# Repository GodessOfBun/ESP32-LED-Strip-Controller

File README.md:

## Introduction:

This ESP32-C2 Based board is designed to control up to 5 channels of an LED Strip. Each channel is in theory capable of 4A up to 24V with the total current drawn from the board not exceeding 5A. Although in theory there isn't much preventing it from reaching 8A current(eFuse max) other than trace width and the bulk capacitor and so on.
Mosfet remains below 50c with a 99% duty cycle at 2.4A/24v @ 25KHz in testing. In theory, according to my calculations, it can easily handle 4A or even 4.5A/5A. above 4A is not recommended. It is compatible with Matter (using the code I'm too eepy and busy to upload right now) and HA with ESPHome. If you use HA  you might as well save yourself the trouble and use ESPHome as Matter can have it's own shortcomings.

Measured Channel FET rise time: 12.5ns.

eFuse can be skipped by shorting the VIN to EFUSE to the output with a wire.

The board is designed for 25KHz in mind but can be used with a lower or higher frequency within reason.

You can leave unused channnels empty and not solder them to save on cost. 

The EFUSE is connfigured to be triggered at 5.51A. It features a 150ms-300ms~ soft-start to prevent sparks when connecting the power.

Note: It features a 0201 test LED originally used as a fun challenge for soldering. I suggest changing it to a 0602/0402 package if using it in practice or debugging with it as it can be very challenging to solder.

A IPEX connector is used to debug and monitor the 3.3v rail ripple and transient performance. Note however that the 50 ohm termination seems to not be working, I will confirm why when the project is finished as it's not essential and works perfectly fine with a probe tip to BNC adapter as the probe is designed to be purposely lossy and cancel ringing. A BNC to IPEX Cable is recommended. Note that IPEX connectors are not meant for frequent unplugging and replugging. The socket is rated for 30-50 mating cycles

### Notes:
Frequency of 2.2MHz was chosen for the 3.3v rail to improve transient response and performance/size of the buck converter. Efficiency is not a big concern for such an application.
An eFuse (Hot-swap controller) was chosen for this board to prevent sparking upon plugging in and to reduce the required footprint for an ressetable poly fuse that can withstand 40-30v at 5A.

## Potential  Improvemtns:
- [ ] Add a factory reset button seperate from BOOT
- [ ] External antenna instead of built-in PCB
- [ ] Switch from ESP32-C2 to C3 or similiar for better matter compatbility and performance.
- [ ] Use a dedicated ESP32 IC instead of a pre-made module as the PCB is already 4 layers hence the impedance matching is very easy and does not add additional cost.
- [ ] Add a polymer/tantalum bulk cap for esp32 to reduce wifi transmission transients. This will require some consideration to prevent ringing at the output.
- [ ] Calculate and confirm feed-forward capacitor for the 3.3v rail. (It is picked based on gut feeling)
- [ ] Improve hand-solderability, use bigger TVS diodes.
- [ ] Add jumper for 3.3v from programming header.
- [ ] (?) Debug LED for each channel
- [ ] (?) RGB Indicator LED for when WiFI is connected and device is commisioned.
- [ ] (?) Software based SSFM solution for each channel to reduce EMI emitted from the LED Strips as they are difficult to shield and user assembled. For a simpler but less effective solution, Each channel can operate at a slightly different ferquency.
- [ ] (?) eFuse skip jumper.

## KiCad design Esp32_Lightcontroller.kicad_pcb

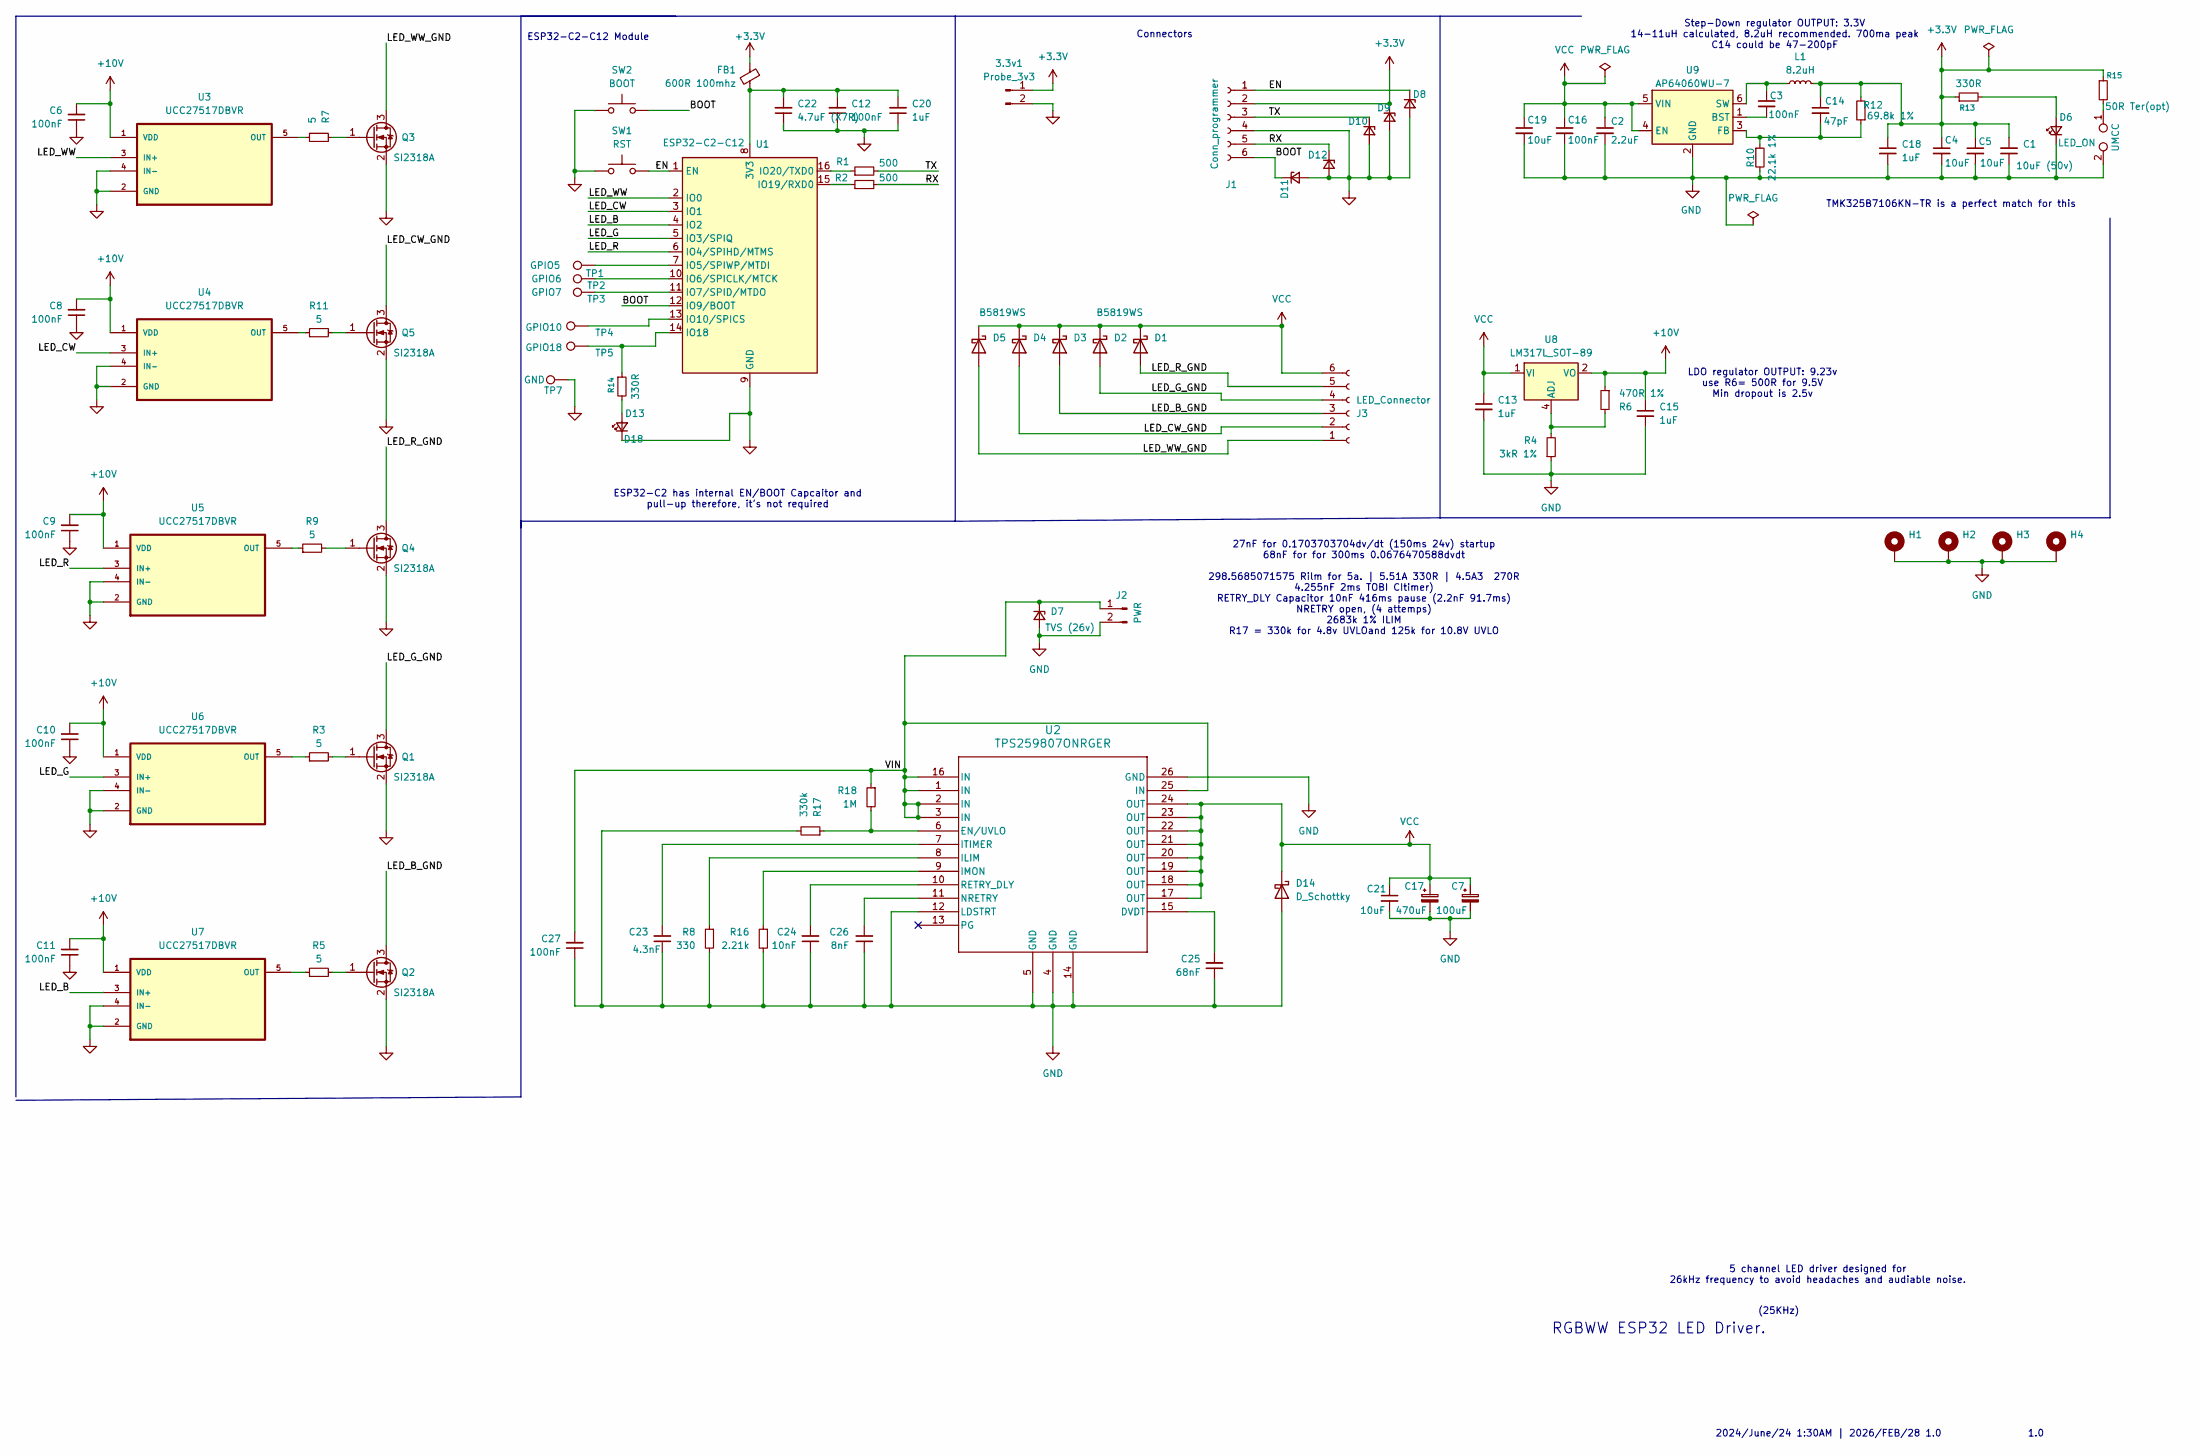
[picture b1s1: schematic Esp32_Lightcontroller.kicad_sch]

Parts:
3.3v1: Probe_3v3; Scope_probe_pad
C1: 10uF (50v); C_1210_3225Metric
C2: 2.2uF; C_1206_3216Metric
C3, C12, C16: 100nF; C_0603_1608Metric
C4, C5, C19, C21: 10uF; C_1210_3225Metric
C6, C8, C9, C10, C11, C27: 100nF; C_0402_1005Metric
C7: 100uF; CP_Elec_6.3x7.7
C13, C18, C20: 1uF; C_0805_2012Metric
C14: 47pF; C_0402_1005Metric
C15: 1uF; C_1206_3216Metric
C17: 470uF; CP_Radial_D10.0mm_P5.00mm
C22: 4.7uF (X7R); C_0805_2012Metric
C23: 4.3nF; C_0402_1005Metric
C24: 10nF; C_0402_1005Metric
C25: 68nF; C_0402_1005Metric
C26: 8nF; C_0402_1005Metric
D1, D5: B5819WS; D_SOD-323
D2, D3, D4: 1N5819WS; D_SOD-323
D6: LED_ON; LED_0603_1608Metric
D7: TVS (26v); D_SOD-123F
D8, D9, D10, D11, D12: 5v; D_SOD-523
D13: D18; LED_0201_0603Metric
D14: D_Schottky; D_SOD-123
FB1: 600R 100mhz; Ferrite_0603_1608Metric
H1, H2, H3, H4: MountingHole_Pad; MountingHole_3.2mm_M3_DIN965_Pad_TopBottom
J1: Conn_programmer; PinHeader_2x03_P1.27mm_Vertical
J2: PWR; TerminalBlock_CUI_TB007-508-02_1x02_P5.08mm_Horizontal
J3: LED_Connector; TerminalBlock_MaiXu_MX126-5.0-06P_1x06_P5.00mm
L1: 8.2uH; L_Coilcraft_XAL6060-XXX
Q1, Q2, Q3, Q4, Q5: SI2318A; SOT-23
R1, R2: 500; R_0603_1608Metric
R3, R5, R7, R9, R11: 5; R_0603_1608Metric
R4: 3kR 1%; R_0603_1608Metric
R6: 470R 1%; R_0603_1608Metric
R8: 330; R_0603_1608Metric
R10: 22.1k 1%; R_0603_1608Metric
R12: 69.8k 1%; R_0603_1608Metric
R13: 330R; R_0603_1608Metric
R14: 330R; R_0201_0603Metric
R15: 50R Ter(opt); R_0603_1608Metric
R16: 2.21k; R_0603_1608Metric
R17: 330k; R_0603_1608Metric
R18: 1M; R_0603_1608Metric
SW1: RST; SW_Push_SPST_NO_Alps_SKRK
SW2: BOOT; SW_Push_SPST_NO_Alps_SKRK
TP1: GPIO5; TestPoint_Pad_D1.5mm
TP2: GPIO6; TestPoint_Pad_D1.5mm
TP3: GPIO7; TestPoint_Pad_D1.5mm
TP4: GPIO10; TestPoint_Pad_D1.5mm
TP5: GPIO18; TestPoint_Pad_D1.5mm
TP6: UMCC; U.FL_Molex_MCRF_73412-0110_Vertical
TP7: GND; TestPoint_Pad_D1.5mm
U1: ESP32-C2-C12
U2: TPS259807ONRGER; VQFN24_RGE_TEX
U3, U4, U5, U6, U7: UCC27517DBVR; SOT95P280X145-5N; DigiKey_Part_Number 296-39527-1-ND
U8: LM317L_SOT-89; SOIC-8_3.9x4.9mm_P1.27mm
U9: AP64060WU-7; TSOT-23-6

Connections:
+3.3V: 3.3v1.1, C1.2, C4.1, C5.1, C14.1, C18.1, D9.1 (K), FB1.1, J1.2, L1.2, R12.2, R13.1, R15.1
+10V: C6.2, C8.2, C9.2, C10.2, C11.2, C15.1, R6.1, U3.1 (VDD), U4.1 (VDD), U5.1 (VDD), U6.1 (VDD), U7.1 (VDD), U8.2 (VO), U8.3 (VO), U8.6 (VO), U8.7 (VO)
/BOOT: D11.1 (K), J1.6, SW2.2, U1.12 (IO9/BOOT)
/EN: D8.1 (K), J1.1, SW1.2, U1.1 (EN)
/LED_B: U1.4 (IO2), U7.3 (IN+)
/LED_B_GND: D3.2 (A), J3.3, Q2.3 (D)
/LED_CW: U1.3 (IO1), U4.3 (IN+)
/LED_CW_GND: D4.2 (A), J3.2, Q5.3 (D)
/LED_G: U1.5 (IO3/SPIQ), U6.3 (IN+)
/LED_G_GND: D2.2 (A), J3.4, Q1.3 (D)
/LED_R: U1.6 (IO4/SPIHD/MTMS), U5.3 (IN+)
/LED_R_GND: D1.2 (A), J3.5, Q4.3 (D)
/LED_WW: U1.2 (IO0), U3.3 (IN+)
/LED_WW_GND: D5.2 (A), J3.1, Q3.3 (D)
/RX: D12.1 (K), J1.5, R2.2
/TX: D10.1 (K), J1.3, R1.2
/VIN: C27.2, D7.1 (K), J2.1, R18.1, U2.1 (IN), U2.2 (IN), U2.3 (IN), U2.16 (IN), U2.25 (IN)
GND: 3.3v1.2, C1.1, C2.2, C4.2, C5.2, C6.1, C7.2, C8.1, C9.1, C10.1, C11.1, C12.1, C13.2, C15.2, C16.2, C17.2, C18.2, C19.2, C20.1, C21.2, C22.1, C23.1, C24.1, C25.1, C26.1, C27.1, D6.1 (K), D7.2 (A), D8.2 (A), D9.2 (A), D10.2 (A), D11.2 (A), D12.2 (A), D13.1 (K), D14.2 (A), H1.1, H2.1, H3.1, H4.1, J1.4, J2.2, Q1.2 (S), Q2.2 (S), Q3.2 (S), Q4.2 (S), Q5.2 (S), R4.1, R8.2, R10.2, R16.2, R17.2, SW1.1, SW2.1, TP6.2, TP7.1, U1.9 (GND), U2.4 (GND), U2.5 (GND), U2.12 (LDSTRT), U2.14 (GND), U2.26 (GND), U3.2 (GND), U3.4 (IN-), U4.2 (GND), U4.4 (IN-), U5.2 (GND), U5.4 (IN-), U6.2 (GND), U6.4 (IN-), U7.2 (GND), U7.4 (IN-), U9.2 (GND)
unnamed: D6.2 (A), R13.2
unnamed: D13.2 (A), R14.2
unnamed: Q1.1 (G), R3.2
unnamed: Q2.1 (G), R5.2
unnamed: Q3.1 (G), R7.2
unnamed: Q4.1 (G), R9.2
unnamed: Q5.1 (G), R11.2
unnamed: R15.2, TP6.1
unnamed: C12.2, C20.2, C22.2, FB1.2, U1.8 (3V3)
unnamed: TP1.1, U1.7 (IO5/SPIWP/MTDI)
unnamed: TP2.1, U1.10 (IO6/SPICLK/MTCK)
unnamed: TP3.1, U1.11 (IO7/SPID/MTDO)
unnamed: TP4.1, U1.13 (IO10/SPICS)
unnamed: R14.1, TP5.1, U1.14 (IO18)
unnamed: R2.1, U1.15 (IO19/RXD0)
unnamed: R1.1, U1.16 (IO20/TXD0)
unnamed: C25.2, U2.15 (DVDT)
unnamed: R17.1, R18.2, U2.6 (EN/UVLO)
unnamed: R8.1, U2.8 (ILIM)
unnamed: R16.1, U2.9 (IMON)
unnamed: C23.2, U2.7 (ITIMER)
unnamed: C26.2, U2.11 (NRETRY)
unnamed: C24.2, U2.10 (RETRY_DLY)
unnamed: R7.1, U3.5 (OUT)
unnamed: R11.1, U4.5 (OUT)
unnamed: R9.1, U5.5 (OUT)
unnamed: R3.1, U6.5 (OUT)
unnamed: R5.1, U7.5 (OUT)
unnamed: R4.2, R6.2, U8.4 (ADJ)
unnamed: C3.2, U9.1 (BST)
unnamed: C14.2, R10.1, R12.1, U9.3 (FB)
unnamed: C3.1, L1.1, U9.6 (SW)
VCC: C2.1, C7.1, C13.1, C16.1, C17.1, C19.1, C21.1, D1.1 (K), D2.1 (K), D3.1 (K), D4.1 (K), D5.1 (K), D14.1 (K), J3.6, U2.17 (OUT), U2.18 (OUT), U2.19 (OUT), U2.20 (OUT), U2.21 (OUT), U2.22 (OUT), U2.23 (OUT), U2.24 (OUT), U8.1 (VI), U9.4 (EN), U9.5 (VIN)

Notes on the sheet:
LDO regulator OUTPUT: 9.23v use R6= 500R for 9.5V Min dropout is 2.5v
5 channel LED driver designed for 26kHz frequency to avoid headaches and audiable noise.
ESP32-C2 has internal EN/BOOT Capcaitor and pull-up therefore, it's not required
Step-Down regulator OUTPUT: 3.3V 14-11uH calculated, 8.2uH recommended. 700ma peak C14 could be 47-200pF
ESP32-C2-C12 Module
(25KHz)
TMK325B7106KN-TR is a perfect match for this
2024/June/24 1:30AM | 2026/FEB/28 1.0
RGBWW ESP32 LED Driver.
27nF for 0.1703703704dv/dt (150ms 24v) startup 68nF for for 300ms 0.0676470588dvdt 298.5685071575 Rilm for 5a. | 5.51A 330R | 4.5A3 270R 4.255nF 2ms TOBI CItimer) RETRY_DLY Capacitor 10nF 416ms pause (2.2nF 91.7ms) NRETRY open, (4 attemps) 2683k 1% ILIM R17 = 330k for 4.8v UVLOand 125k for 10.8V UV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
1.0
Connectors

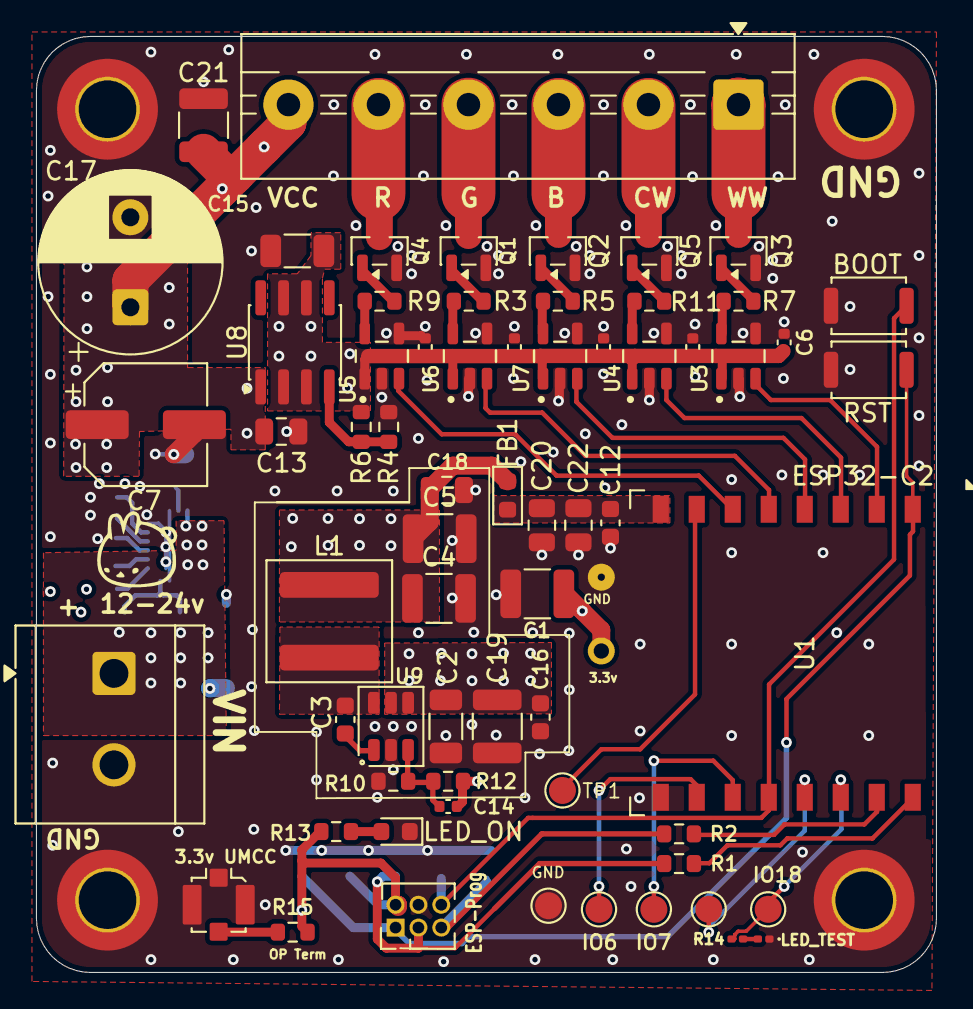
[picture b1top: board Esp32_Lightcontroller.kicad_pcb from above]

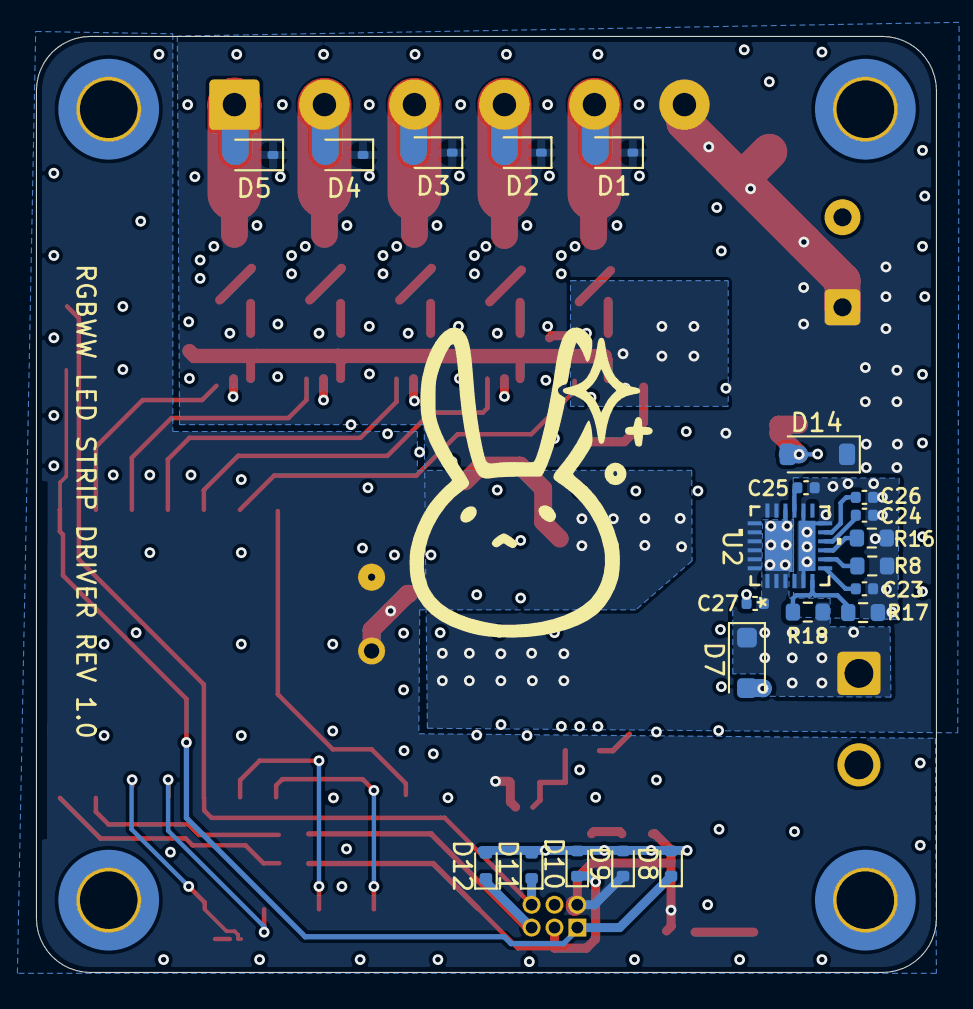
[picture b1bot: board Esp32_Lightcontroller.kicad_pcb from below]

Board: 4 copper layers, 50.0 x 52.0 mm, 92 parts (22 on the bottom side), 51 nets.

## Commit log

2026-02-26 Added .gitignore
2026-02-26 Create README.md
    Added README.md
2026-02-26 Update README.md
    Added image to the README.md file.
2026-03-05 Update README.md
    updated README
2026-04-08 Refinements
